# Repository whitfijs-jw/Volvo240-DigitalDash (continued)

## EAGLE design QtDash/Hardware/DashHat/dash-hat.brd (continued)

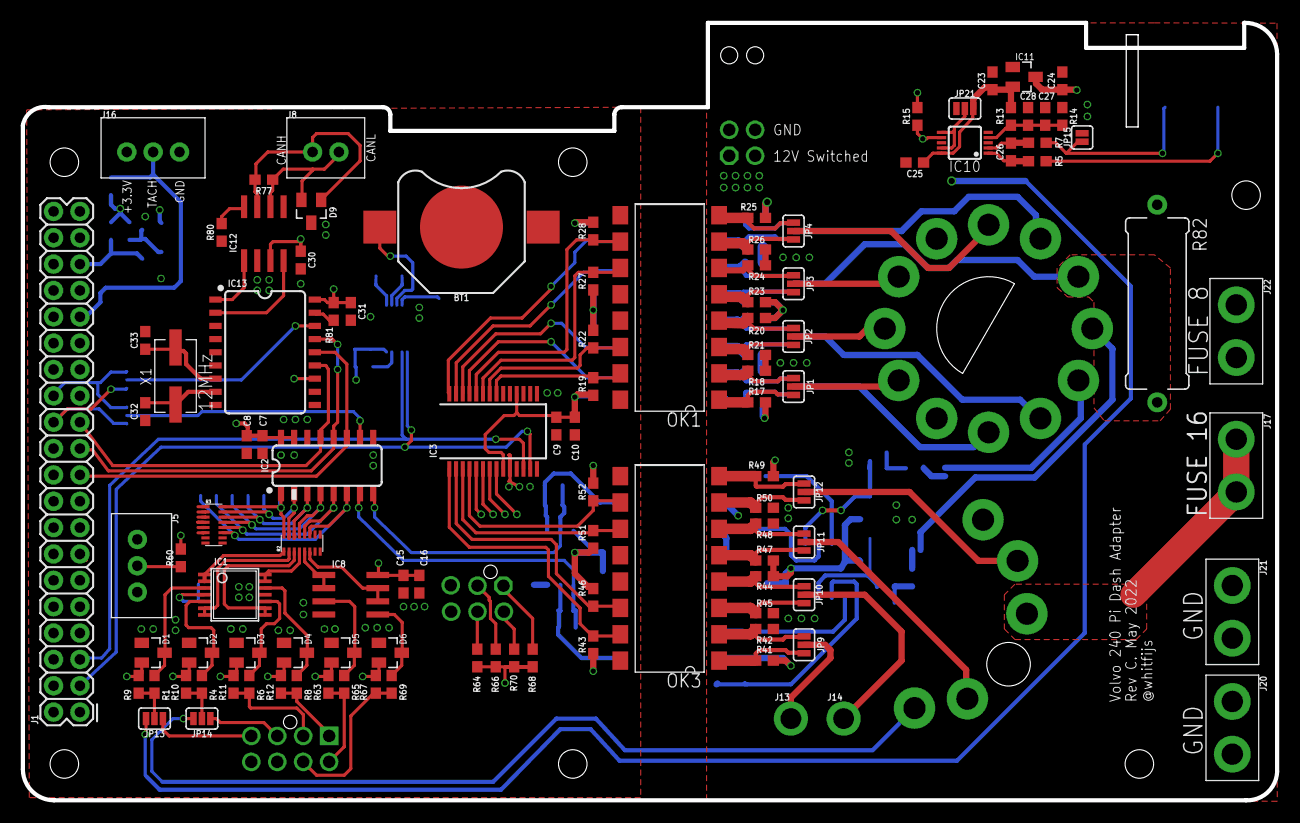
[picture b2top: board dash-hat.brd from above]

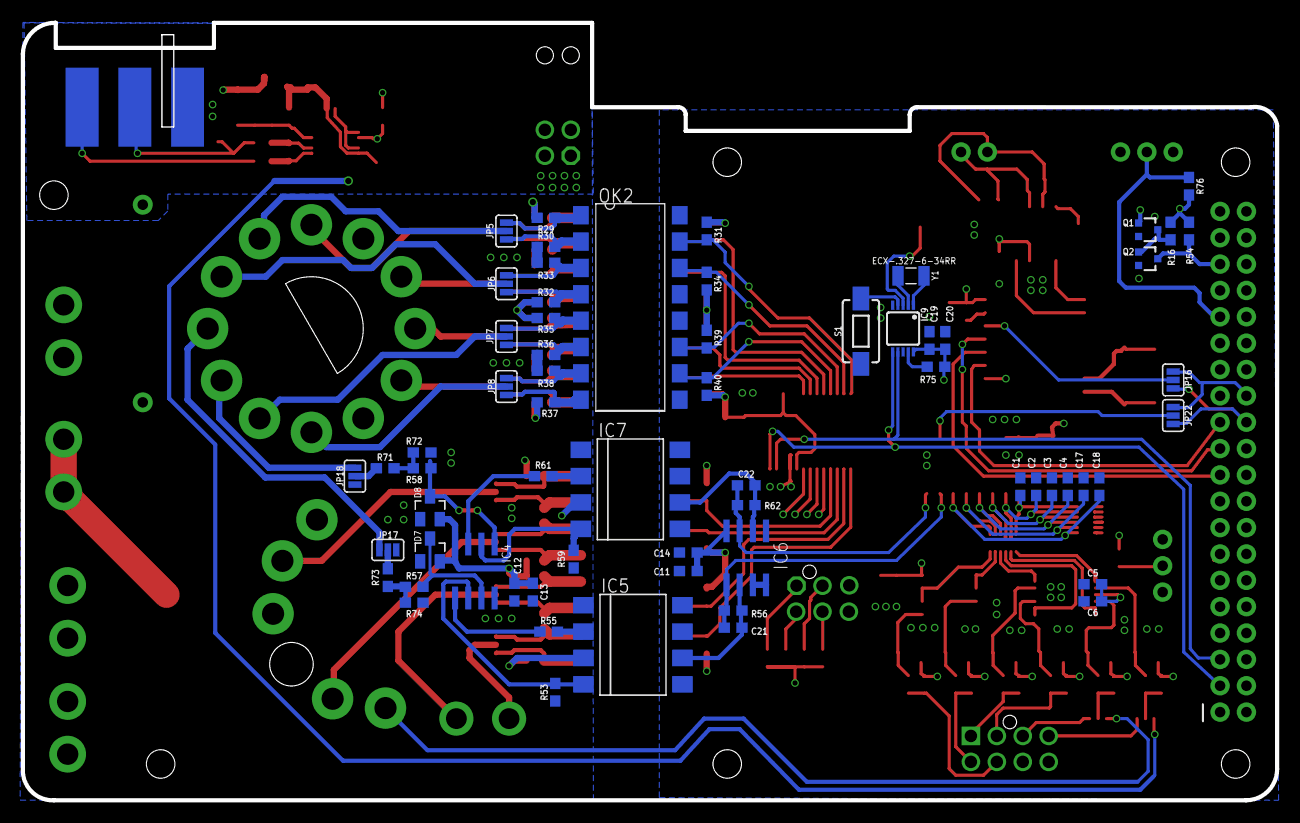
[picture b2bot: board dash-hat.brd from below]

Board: 4 copper layers, 120.9 x 74.9 mm, 179 parts (65 on the bottom side), 139 nets.

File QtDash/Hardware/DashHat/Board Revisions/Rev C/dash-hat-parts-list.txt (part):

Partlist exported from /home/whitfijs/git/Volvo240-DigitalDash/QtDash/Hardware/DashHat/dash-hat.sch at 5/19/22 10:42 PM

Qty Value                Device                              Package                      Parts                                                                                                        Description                                                                                                      MF        MPN           OC_FARNELL OC_NEWARK PROD_ID     SF_SKU    TOLERANCE VALUE          VOLTAGE
1                        BATTERY-12MM_SMD                    BATTCON_12MM                 BT1                                                                                                          Battery - Single Cell                                                                                                                                         BATT-08044  PRT-10592                                 
2                        CONN_01PTH_2MM                      1X01_2MM                     J13, J14                                                                                                     Single connection point. Often used as Generic Header-pin footprint for 0.1 inch spaced/style header connections                                                                                                    
1                        CONN_02                             1X02                         J8                                                                                                           Multi connection point. Often used as Generic Header-pin footprint for 0.1 inch spaced/style header connections                                                                                                     
4                        CONN_02PTH4                         1X02_XTRA_BIG                J17, J20, J21, J22                                                                                           Multi connection point. Often used as Generic Header-pin footprint for 0.1 inch spaced/style header connections                                                                                                     
8   100R                 RC0603JR-07100RL                    0603                         R1, R4, R6, R8, R57, R58, R65, R69                                                                                                                                                                                                                                                                         100R                  
6   100k 1%              RC0603FR-10100KL                    0603                         R53, R59, R71, R72, R73, R74                                                                                                                                                                                                                                                                               100k 1%               
20  100n                 CL10B104MB8NNNC                     0603                         C1, C2, C3, C4, C5, C7, C9, C11, C12, C15, C17, C18, C19, C21, C22, C23, C25, C27, C30, C31                                                                                                                                                                                                                100n           50V    
2   10k 1%               RC0603FR-1010KL                     0603                         R5, R7                                                                                                                                                                                                                                                                                                     10k 1%                
1   10u                  CL10B106MQ8NRNC                     0603                         C28                                                                                                                                                                                                                                                                                                        10u            6.3V   
1   120 1%               RC0603FR-07120RL                    0603                         R77                                                                                                                                                                                                                                                                                                        120 1%                
1   12MHz                ECS-120-20-3X-TR                    ECS                          X1                                                                                                                                                                                                                                                                                                         12MHz                 
1   15k                  YC248-JR-0715KL                     YC248                        R3                                                                                                                                                                                                                                                                                               5%        15k                   
15  1k                   RC0603JR-071KL                      0603                         R9, R10, R11, R12, R13, R14, R15, R63, R64, R66, R67, R68, R70, R75, R80                                                                                                                                                                                                                                   1k                    
1   1n                   CL10B102KB8NNWC                     0603                         C26                                                                                                                                                                                                                                                                                                        1n             50V    
8   1u                   CL10A105KA8NNNC                     0603                         C6, C8, C10, C13, C14, C16, C20, C24                                                                                                                                                                                                                                                                       1u             25V    
5   20k                  RC0603JR-0720KL                     0603                         R16, R54, R60, R76, R81                                                                                                                                                                                                                                                                                    20k                   
2   20k 1%               RC0603FR-0720KL                     0603                         R56, R62                                                                                                                                                                                                                                                                                                   20k 1%                
2   22p                  CL10C220JB81PNC                     0603                         C32, C33                                                                                                                                                                                                                                                                                                   22p            50V    
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
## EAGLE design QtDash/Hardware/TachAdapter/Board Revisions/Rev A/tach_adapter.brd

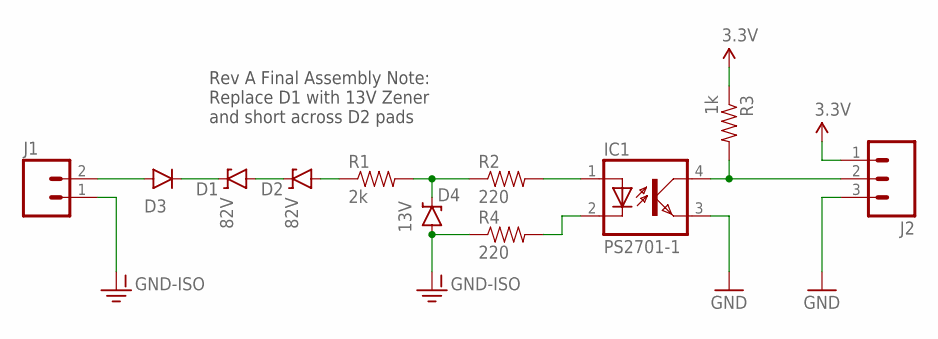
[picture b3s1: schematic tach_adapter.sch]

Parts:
D1, D2: 82V; SMB-DIODE
D3: DIODESMA; SMA-DIODE
D4: 13V; SMB-DIODE
IC1: PS2701-1; 4-SMD
J1: M02PTH3; 1X02_LONGPADS
J2: M03LONGPADS; 1X03_LONGPADS
R1: 2k; 1206
R2, R4: 220; 1206
R3: 1k; 1206

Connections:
3.3V: J2.1, R3.1
GND: IC1.3 (EMIT), J2.3
GND-ISO: D4.A, J1.1, R4.1
unnamed: D1.C, D3.C
unnamed: D1.A, D2.C
unnamed: D2.A, R1.1
unnamed: D4.C, R1.2, R2.1
unnamed: IC1.1 (A), R2.2
unnamed: IC1.2 (C), R4.2
unnamed: IC1.4 (COL), J2.2, R3.2
unnamed: D3.A, J1.2

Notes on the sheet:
Rev A Final Assembly Note: Replace D1 with 13V Zener and short across D2 pads

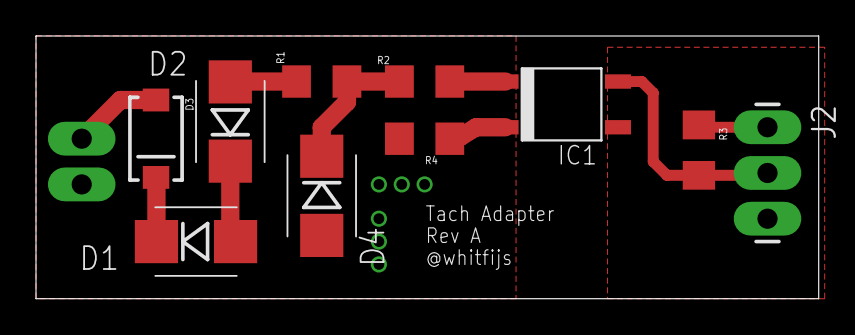
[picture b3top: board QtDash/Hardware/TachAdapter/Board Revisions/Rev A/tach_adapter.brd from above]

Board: 2 copper layers, 43.5 x 14.6 mm, 11 parts (0 on the bottom side), 11 nets.

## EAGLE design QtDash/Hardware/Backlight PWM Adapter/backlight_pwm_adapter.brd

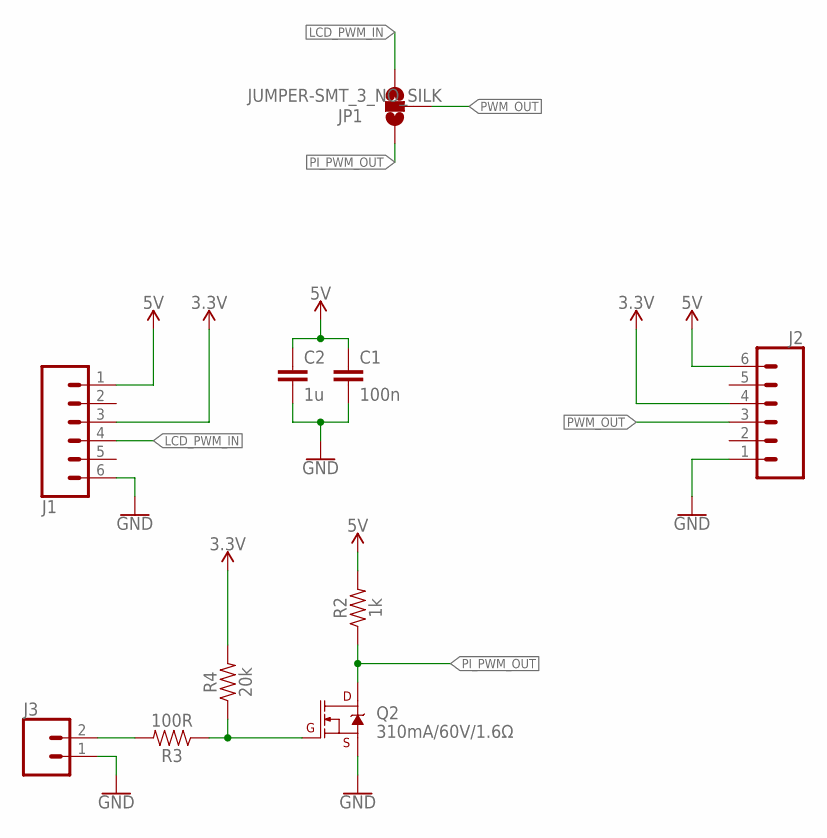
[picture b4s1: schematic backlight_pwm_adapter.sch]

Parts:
C1: 100n; 0603
C2: 1u; 0603
J1, J2: CONN_06; 140-506-417-060
J3: CONN_02; 1X02
JP1: JUMPER-SMT_3_NO_SILK; SMT-JUMPER_3_NO_SILK
Q2: 310mA/60V/1.6Ω; SOT323
R2: 1k; 0603
R3: 100R; 0603
R4: 20k; 0603

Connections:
3.3V: J1.3, J2.4, R4.2
5V: C1.1, C2.1, J1.1, J2.6, R2.2
GND: C1.2, C2.2, J1.6, J2.1, J3.1, Q2.2 (S)
LCD_PWM_IN: J1.4, JP1.3
unnamed: J3.2, R3.2
unnamed: Q2.1 (G), R3.1, R4.1
PI_PWM_OUT: JP1.1, Q2.3 (D), R2.1
PWM_OUT: J2.3, JP1.2

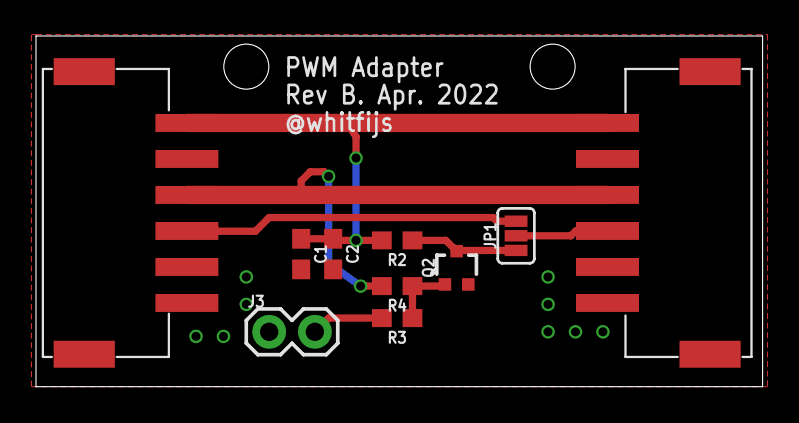
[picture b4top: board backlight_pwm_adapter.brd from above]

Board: 2 copper layers, 40.4 x 19.5 mm, 10 parts (0 on the bottom side), 8 nets.

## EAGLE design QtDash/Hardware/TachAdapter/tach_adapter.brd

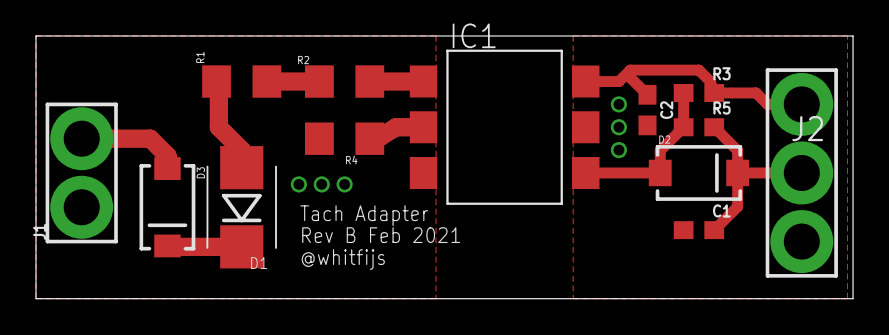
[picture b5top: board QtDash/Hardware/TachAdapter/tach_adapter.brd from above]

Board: 2 copper layers, 45.4 x 14.6 mm, 13 parts (0 on the bottom side), 11 nets.

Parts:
C1: 10n; 0603
C2: 100n; 0603
D1: 13V; SMB-DIODE
D2, D3: SMA-DIODE
IC1: H11L1SR2VM; 6-SMD
J1: 1X02_LARGE
J2: 1X03_LARGE
R1: 2k; 1206
R2, R4: 220; 1206
R3, R5: 1k; 0603

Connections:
3.3V: C2.1, IC1.6, J2.1, R3.1
GND: C1.2, C2.2, IC1.5, J2.3
GND-ISO: J1.1, R4.1
unnamed: D1.C, D3.C
unnamed: C1.1, D2.C, J2.2, R5.2
unnamed: D1.A, R1.1
unnamed: R1.2, R2.1
unnamed: IC1.1, R2.2
unnamed: IC1.2, R4.2
unnamed: D2.A, IC1.4, R3.2, R5.1
unnamed: D3.A, J1.2

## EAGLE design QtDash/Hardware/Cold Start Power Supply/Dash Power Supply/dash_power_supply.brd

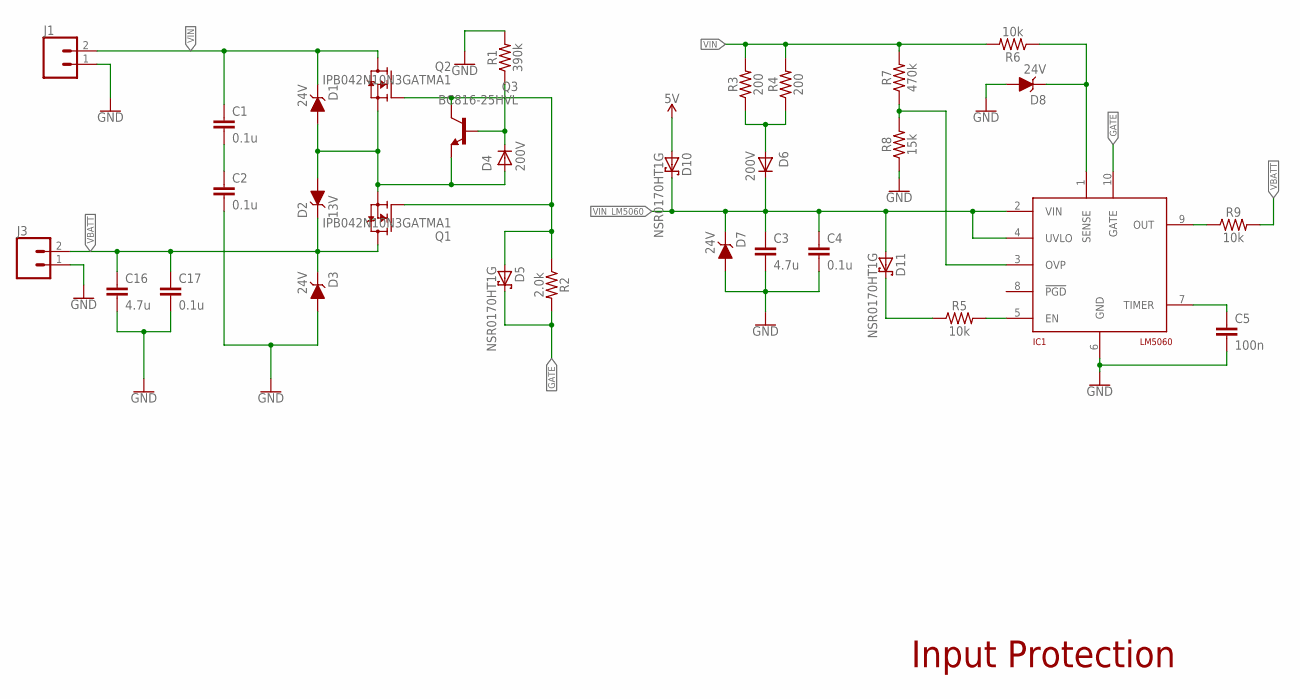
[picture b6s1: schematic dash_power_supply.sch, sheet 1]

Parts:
C1, C2, C4, C17: 0.1u; C1210
C3, C16: 4.7u; C1210
C5: 100n; 0603
D1, D3: 24V; SMC
D2: 13V; D0-219AB
D4, D6: 200V; D0-219AB
D5, D10, D11: NSR0170HT1G; SOD-323
D7, D8: 24V; SMA
IC1: LM5060; VSSOP-10
J1, J3: CONN_02PTH4; 1X02_XTRA_BIG
Q1, Q2: IPB042N10N3GATMA1; TO263
Q3: BC816-25HVL; SOT23
R1: 390k; 0603
R2: 2.0k; 0603
R3, R4: 200; 1206
R5, R6, R9: 10k; 0603
R7: 470k; 0603
R8: 15k; 0603

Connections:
5V: D10.A; also elsewhere on the board
G: D5.A, Q1.1 (G), Q2.1 (G), Q3.3 (C), R2.1
GATE: D5.C, IC1.10 (GATE), R2.2
GND: C2.2, C3.2, C4.2, C5.2, C16.2, C17.2, D3.A, D7.A, D8.A, IC1.6 (GND), J1.1, J3.1, R1.2, R8.1; also elsewhere on the board
unnamed: C1.2, C2.1
unnamed: IC1.5 (EN), R5.2
unnamed: D6.A, R3.1, R4.1
unnamed: D8.C, IC1.1 (SENSE), R6.1
unnamed: D4.C, Q3.1 (B), R1.1
unnamed: IC1.3 (OVP), R7.1, R8.2
unnamed: C5.1, IC1.7 (TIMER)
unnamed: IC1.9 (OUT), R9.1
unnamed: D11.C, R5.1
VBATT: C16.1, C17.1, D2.C, D3.C, J3.2, Q1.3 (D), R9.2; also elsewhere on the board
VIN: C1.1, D1.C, J1.2, Q2.3 (D), R3.2, R4.2, R6.2, R7.2
VIN_INTERNAL: D1.A, D2.A, D4.A, Q1.2 (S), Q2.2 (S), Q3.2 (E)
VIN_LM5060: C3.1, C4.1, D6.C, D7.C, D10.C, D11.A, IC1.2 (VIN), IC1.4 (UVLO)

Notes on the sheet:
Input Protection

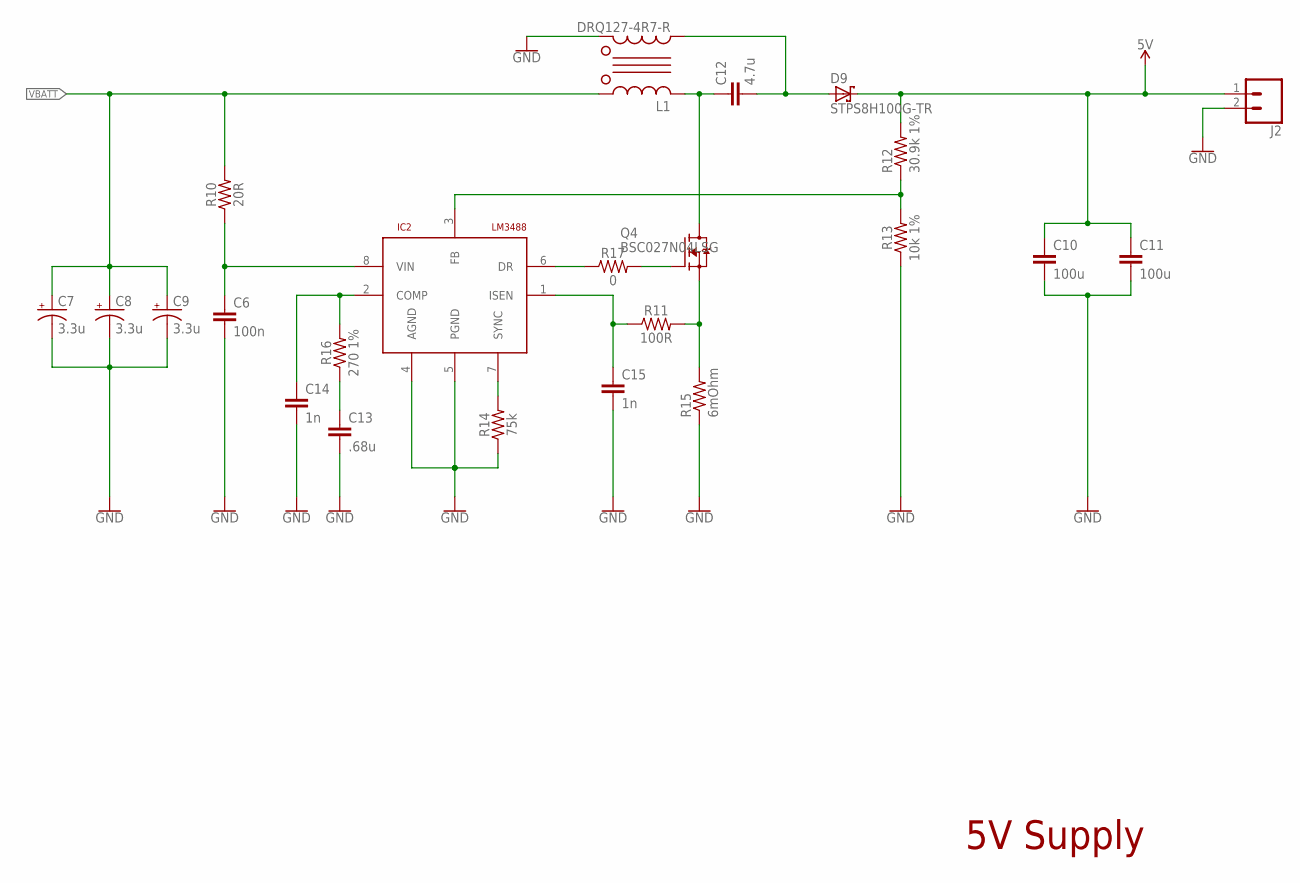
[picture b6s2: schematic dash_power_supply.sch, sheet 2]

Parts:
C6: 100n; 0603
C7, C8, C9: 3.3u; PANASONIC_C
C10, C11: 100u; C1210
C12: 4.7u; 0603
C13: .68u; 0603
C14, C15: 1n; 0603
D9: STPS8H100G-TR; TO263
IC2: LM3488; VSSOP-8
J2: CONN_02PTH4; 1X02_XTRA_BIG
L1: DRQ127-4R7-R; DRQ127
Q4: BSC027N04LSG; TDSON
R10: 20R; 0603
R11: 100R; 0603
R12: 30.9k 1%; R1206
R13: 10k 1%; 0603
R14: 75k; 0603
R15: 6mOhm; 3216
R16: 270 1%; 0603
R17: 0; 0603

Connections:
5V: C10.1, C11.1, D9.3 (C), J2.1, R12.2; also elsewhere on the board
GND: C6.2, C7.-, C8.-, C9.-, C10.2, C11.2, C13.2, C14.2, C15.2, IC2.4 (AGND), IC2.5 (PGND), J2.2, L1.2, R13.1, R14.1, R15.1; also elsewhere on the board
unnamed: Q4.4 (G), R17.2
unnamed: C6.1, IC2.8 (VIN), R10.1
unnamed: IC2.3 (FB), R12.1, R13.2
unnamed: IC2.6 (DR), R17.1
unnamed: C15.1, IC2.1 (ISEN), R11.1
unnamed: Q4.1 (S), Q4.2 (S), Q4.3 (S), R11.2, R15.2
unnamed: C12.1, L1.3, Q4.5 (D)
unnamed: C12.2, D9.2 (A), L1.4
unnamed: C14.1, IC2.2 (COMP), R16.2
unnamed: C13.1, R16.1
unnamed: IC2.7 (SYNC), R14.2
VBATT: C7.+, C8.+, C9.+, L1.1, R10.2; also elsewhere on the board

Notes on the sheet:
5V Supply

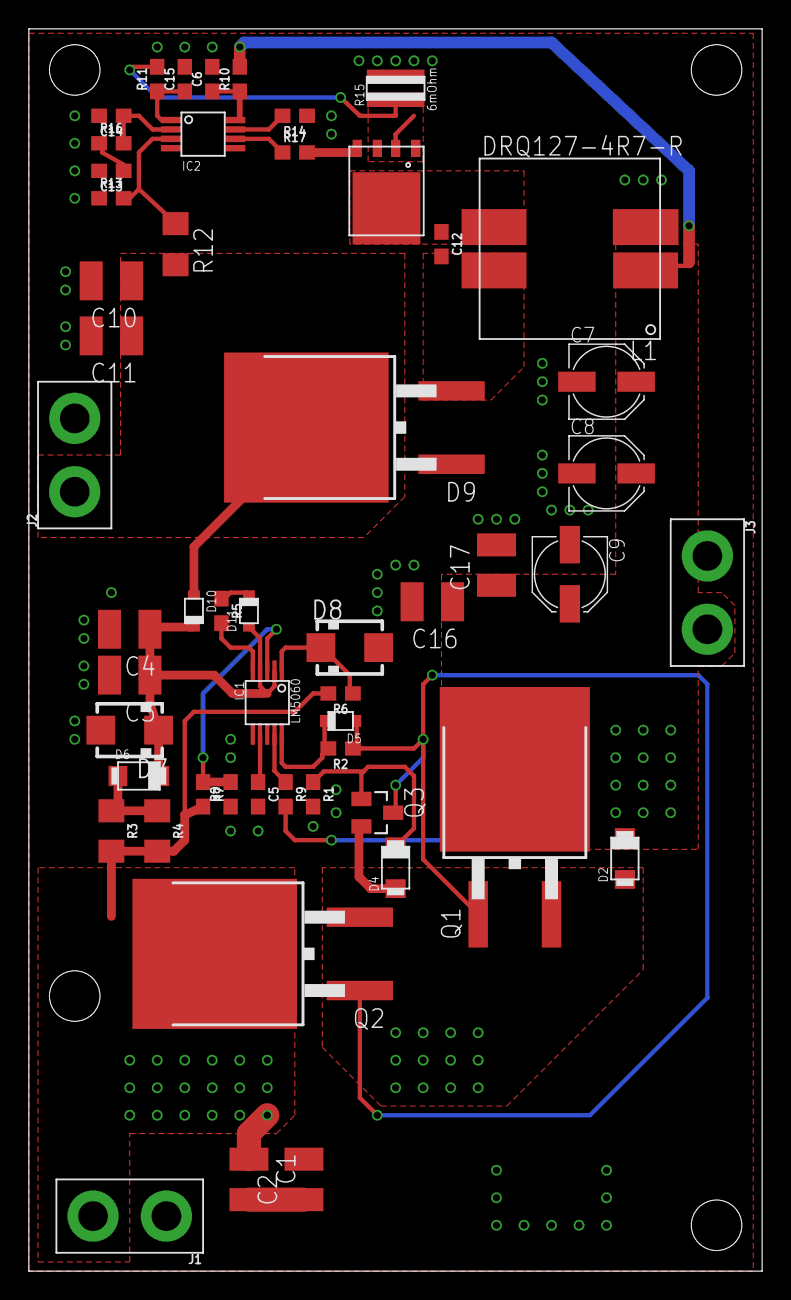
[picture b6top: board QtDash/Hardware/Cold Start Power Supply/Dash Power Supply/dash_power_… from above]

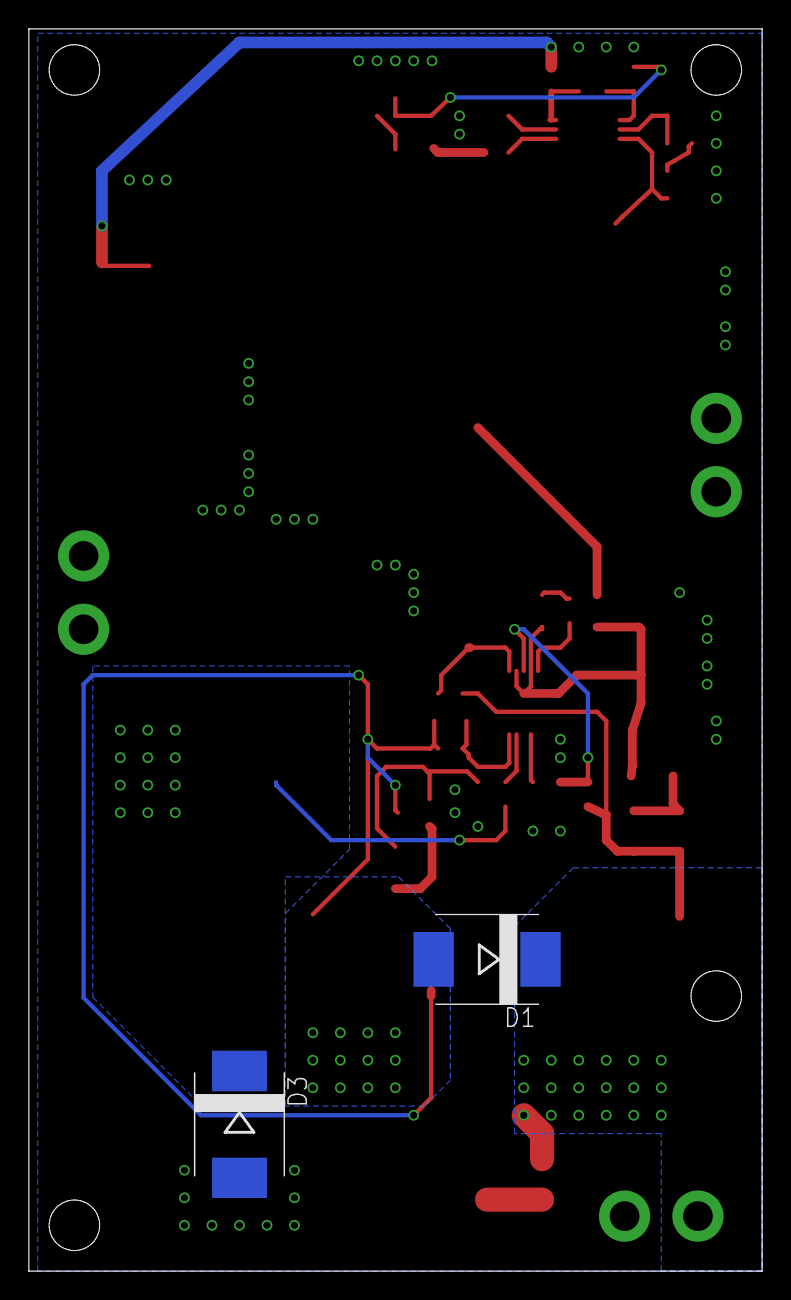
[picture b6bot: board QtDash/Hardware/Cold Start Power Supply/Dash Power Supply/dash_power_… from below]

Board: 2 copper layers, 50.8 x 86.0 mm, 55 parts (2 on the bottom side), 28 nets.

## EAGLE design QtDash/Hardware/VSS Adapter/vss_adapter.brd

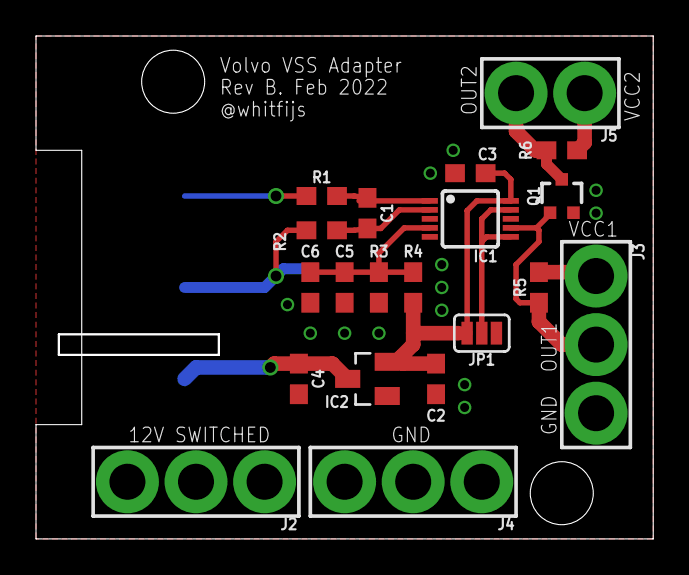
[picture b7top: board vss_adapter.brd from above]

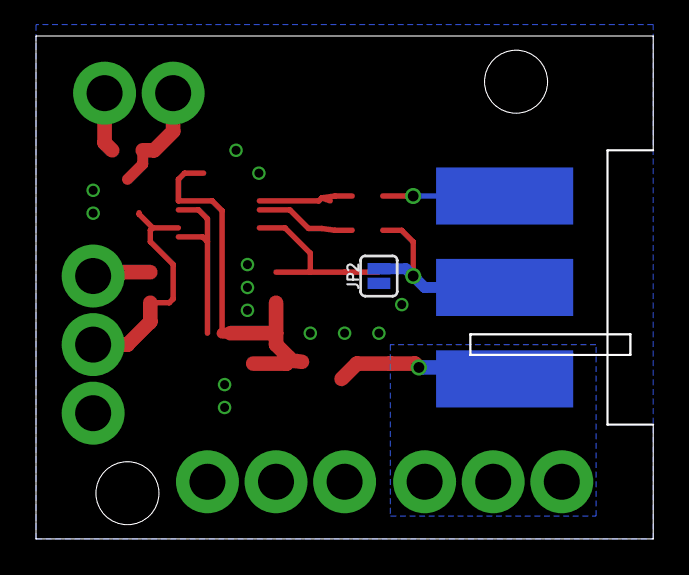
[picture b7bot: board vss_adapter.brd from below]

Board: 2 copper layers, 34.3 x 27.9 mm, 22 parts (2 on the bottom side), 13 nets.

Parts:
C1: 1n; 0603
C2, C3, C6: 100n; 0603
C4: 1u; 0603
C5: 10u; 0603
IC1: MAX9924; UMAX10
IC2: ZXTR2105FQ; SOT23
J1: VOLVO_CONN_VSS
J2, J3, J4: 1X03_LARGE
J5: 1X02_LARGE
JP1: ZERO_EN; SMT-JUMPER_3_NO_SILK
JP2: VSS-_GND; SMT-JUMPER_2_NO_SILK
Q1: 310mA/60V/1.6Ω; SOT323
R1, R2, R5, R6: 10k 1%; 0603
R3, R4: 1k; 0603

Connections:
5V: C2.1, C3.1, IC1.10, IC2.2, JP1.3, R4.1
GND: C2.2, C3.2, C4.2, C5.2, C6.2, IC1.5, IC2.1, J3.3, J4.1, J4.2, J4.3, JP1.1, JP2.1, Q1.2, R3.1
IN+: C1.1, IC1.1, R1.2
IN-: C1.2, IC1.2, R2.2
unnamed: C5.1, C6.1, IC1.4, R3.2, R4.2
unnamed: IC1.6, IC1.9, JP1.2
VCC_1: J3.1, R5.2
VCC_2: J5.1, R6.2
VIN: C4.1, IC2.3, J1.+, J2.1, J2.2, J2.3
VSS2_OUT: J5.2, Q1.3, R6.1
VSS+: J1.G, R1.1
VSS-: J1.1, JP2.2, R2.1
VSS_OUT: IC1.7, J3.2, Q1.1, R5.1

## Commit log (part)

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2022-01-21 - moved dash lights over to fast timer -- indicators might not respond to fast blinkers - droped medium timer to 150msec update
2022-01-23 topic/new-gauge-designs: - added clockwise/counterclockwise flag to gauge - 850 coolant gauge set to clockwise false so it works? Non lo so.
2022-01-25 bugfix/hardware-revA-issues: - added 0.5mm clearance to screen through holes
2022-01-26 bugfix/hardware-revA-issues: - first draft of mount
2022-01-27 bugfix/hardware-revA-issues: - added outputs solder points for fuse 16 and fuse 8 power - added 12V input solder points switched power? - added some ground vias on for 5V ground return path -- things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
2022-01-28 bugfix/hardware-revA-issues: - added squashfs rootfs to sd card image -- should be able to switch between ext4 and squash using cmdline.txt
2022-02-01 bugfix/hardware-revA-issues: - output of IL300s were oscillating under load -- added 100n capacitor (bodged on revA) - 12V inputs are only 0-3.3V signals -- K3 used to compensate for different for now
2022-02-03 bugfix/hardware-revA-issues: - fixed issues with clock seconds hand going the long way around when crossing from 59 to 0
2022-02-06 - copied revA version of pi adapter into /QtDash/Hardware/DashHat/Board Revisions/Rev A - generated gerbers and schematic pdf -- will need to modify the schematic to reflect what was actually built -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
2022-02-06 - update Board Revisions/Rev A schematic with final assembly values notes on final assembly
2022-02-10 topic/new-gauge-designs: - added shroud things on coolant and temp gauges in rsport cluster - updated fonts in rsport cluster svg
2022-02-11 topic/new-gauge-designs: - messing around with gauge borders - changed r-sport gauge needle color
2022-02-12 bugfix/hardware-revA-issues: - added supply only board for testing separately and more cheaply - added resistor values to cold start board library
2022-02-16 topic/switch-to-64-bit: - buildroot adjusted to work without rpi-userland packages - vc4 and v3d compiled into kernel - qml manually rotated 180 degrees - additional QT_QPA parameters added to init.d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
2022-02-17 bugfix/tach-adapter-updates: - added kicad project for tach adapter -- testing out kicad
2022-02-18 topic/new-gauge-designs: - updated bounds of 850r boost gauge
2022-02-19 topic/sensor-and-gauge-value-conditioning: - re-arranged dash initialization to avoid flippy text during boot
2022-02-20 topic/sensor-and-gauge-value-conditioning: - adjusted K3 value for 12V analog inputs, still not quite right -- consider using polynomial fits - adjusted decimal point values for gauges
2022-02-25 topic/component_optimization: - fixed issue with vss source signal/slot hookup - vss input now working -- tested with function generator
2022-03-01 topic/component-optimization: - 20k resistor on vin of power supply should have been 20R - fixed silk screen on cold start power supply - re-arranged components a via for cleaner return paths
2022-03-01 topic/component-optimization: - added some more output capacitors
2022-03-02 topic/more-accurate-gauge-needles: - tested on pi -- looks good - adjusted widths and colors in 740/940 layout
2022-03-03 topic/tach-adapter-udpates: - added kicad and eagle relevant gitignore fields
2022-03-05 - Filled in documentation for sensor configuration file (config.ini)
2022-03-06 bugfix/gauge-configs-dont-propagate: - ugly solution to convert internal sensor units to display units from config_gauges.ini
2022-03-08 - fixed spacing in README.md
2022-03-14 bugfix/analog-12v-input-linearity-issues: - added datasheets for IL300 alternatives - added .lib file for IL300
2022-03-26 topic/hardware-revb-support: - fixed text scaling for warning light
2022-03-30 topic/hardware-revb-support: - added writing of odometer value to pi dash - added Q_OBJECT to sensor_odometer to be able to use its writeOdometerValue signal
2022-04-06 topic/rpi4-support: - non-working configs
2022-04-12 topic/backlight-pwm-control: - added 50% backlight output on boot before app takes over (inittab) - changed cmdline.txt to boot from ext4 partition
2022-04-15 topic/rpi4-support: - moved preview image to top
2022-04-23 topic/backlight-pwm-control: - added (weak) pullup on PWM input to PWM adapter board - probably just need to make a backlight driver on the main board
2022-04-28 topic/hardware-revc: - replaced larger molex connector smaller molex connector
2022-04-29 topic/hardware-revc: - small layout changes to the main board
2022-05-04 topic/hardware-revc: - replaced dd with fbv in /sbin/preinit - tested pwm.h changes
2022-05-12 topic/hardware-revc: - added libsocketcan to target packages - added can-utils (to be removed later) - added Qt SerialBus package - added can0 interface bring up in etc/network
2022-05-13 topic/hardware-revc: - added beginngings of QCanBusDevice initialization
2022-05-20 topic/hardware-revc: - added parts list for rev c
2022-06-02 topic/hardware-revc: - gerbers generated for rev c - pcb's ordered from JLC pcb - rev c board preview images generated
2022-07-08 bugfix/hardware-revc-fixes: - added proper CAN support to rpi4 image -- working with MCP2515 on rev C hardware - fixed missing i2cdev package in rpi4 linux image -- mcp23017 working - MCP3208 moved t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
2022-10-03 bugfix/hardware-revc-fixes: - filled in more config unit tests -- temp sensor configs
2022-10-06 bugfix/hardware-revc-fixes: - changed 4-pin user input to 6-pin molex nano-fit connector to accomodate 3.3V and GND
2022-12-28 bugfix/hardware-revc-fixes: - added start out touch panel for 4 user inputs - fixed issues with host dash setup - changed changing of screen to key released and ignore duplicate events
2023-01-16 bugfix/hardware-revc-fixes: - user inputs pins are configurable - user input key mapping is somewhat configurable (Key_Left,Key_Right are needed to changed screens) - updated DashLights to accept gen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
2023-02-07 bugfix/hardware-revc-fixes: - initial value of resistive sensor previousValue was undefined
2023-02-16 feature/long-press-mapping-for-user-inputs-trip-odometer-resetting: - initial go at long press mapped to resetting trip counters - TODO: make long press mapping configurable
2023-03-14 feature-45: - key press on accessory screen cycles main screen (not configurable or very portable)
2023-03-15 feature-45: - added necessary changes to eglfs_hdmi.json and rcS enviroment variables setup to make touch display with with evdev
2023-03-16 feature-45: - added 740/940 style gauges to accessory screen layout -- side screen switches to 740/940 style gauges for 740 and 850 layouts - added 740 style oil temperature gauge
2023-03-16 feature-45: - added p1800 style boost/vaccum gauge and p1800 style clock assets -- no qml element yet
2023-03-18 feature-45: - added r-sport style accessory gauges
2023-04-06 feature/46-pi-zero-support: - added pi0w image configs -- uses rpi4 linux defconfig - image builds but needs to be tested
2023-11-28 50-map-sensor-atmospheric-offset-not-configurable: - updated readme for new options
2023-12-05 50-map-sensor-atmospheric-offset-not-configurable: - updated README to reflect changes in the config for the supply voltage
2023-12-05 topic/update-readme: - started updating readme with features - added more screenshots of dash styles
2023-12-07 topic/update-readme: - formatting changes
2023-12-08 topic/S60R-gauges: - added needle center image to Gauge.qml - added S60R style needle center, looks bad
2023-12-09 topic/S60R-gauges: - fixed voltmeter asset
2023-12-22 topic/documentation-update: - added tach adapter revision documentation for kicad and eagle
2023-12-22 topic/documentation-cleanup: - added 3d models for thickened main screen mounts - added accessory screen mount 3d models
2024-02-18 topic/early-240-cluster: - first draft of early 240 gauges
2024-02-20 topic/early-240-cluster: - started adding warning lights to early 240 layout
2024-02-21 topic/early-240-cluster: - added font for 240 style gauge - small update to gauge creator
2024-02-22 topic/early-240-cluster: - updated later 240-style with updated renders
2024-02-23 topic/early-240-cluster: - added accessory gauges to later 240 style svg
2024-02-24 topic/early-240-cluster: - attempted to get things sorted out on early 240 cluster
2024-02-26 topic/early-240-cluster: - updated README
2024-02-27 topic/early-240-cluster: - added border to early 240 cluster
2024-02-27 topic/early-240-cluster: - some changes to how the speedo model max and units get set
2024-03-03 topic/delegate-restructuring: - started add kph alternatives to speedometers
2024-03-03 topic/delegate-restructuring: - cleaned up resources that were not being used
2024-03-04 topic/delegate-restructuring: - fixed some gauge ranges in the rsport layout
2024-03-05 topic/delegate-restructuring: - fixed p1800 center gauge scaling
2024-03-10 55-adc-voltage-calculation-incorrect: - fixed issue with voltmeter calculation after testing in car
2024-03-11 topic/accessory-gauge-units: - updated 740/940 style oil temp gauge to include C units
2024-03-11 topic/accessory-gauge-units: - added support for "km/h" to be used as well as "kph"
2024-03-12 topic/accessory-gauge-units: - fixed integer truncating in gauge min/max values - added default values for given units to simplify config_gauges.ini
2024-03-13 topic/accessory-gauge-units: - updated README to include gauge configs
2024-03-14 topic/accessory-gauge-units: - fixed min/max angle on rsport coolant temp gauge - added clockwise option to gauge creator
2024-03-26 topic/accessory-gauge-units: - removed all traces of 140 rallye specific accessory gauges
2024-04-04 topic/config-cleanup: - cleaned up config class
2024-04-04 topic/config-cleanup: - event timer cleanup
2024-04-06 topic/config-cleanup: - ntc class cleanup
2024-04-07 topic/config-cleanup: - gps source cleanup
2024-04-10 topic/config-cleanup: - cleaned up sensor utils
2024-04-15 topic/gear-indicator: - starts on test for the gear indicator sensor
2024-06-18 topic/config-cleanup: - added more sanity checks to guage classes
2024-12-22 feature/63: - finally fixed absolute paths in dash host app
2024-12-27 bugfix/r-sport-cluster-boost-gauge-units: - made alternatives for r-sport cluster accessory boost gauge that don't have units
2025-02-01 task/cleanup-dash-class: - changed raw pointers to unique_ptr
2025-02-01 tasks/cleanup-dash-class: - made can sensors a vector of unique_ptr and touched... everything - getting can sensors now returns const pointer from unique_ptr, seems to be ok as it should have probabl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
2025-02-02 feature/72: - added screen rotation config option to config.ini - screen can be rotated to any arbirary angle (0 and 180 would be the obvious choices, but I won't screen shame) - frame buffer is not 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
2025-02-03 feature/70: - finalized build environment setup
2025-02-03 task/ll-cleanup: - LL adc driver cleanup
2025-02-04 task/ll-cleanup: - const cleanup
2025-02-04 task/gauge-sensor-cleanup: - lots of const ref and const function cleanup
2025-02-07 topic/config-sonarqube-cleanup: - fixed const and raw for loop
2025-02-09 topic/misc-cleanup: - make_unique updates
2025-03-08 topic/REV-D-hardware: - first draft of ADC driver for stm32u545 - todo: I2c peripheral implementation
2025-04-15 82-bom-missing: - added one more DNP to tach adapter board
2025-11-18 topic/S60R-gauges: - fixed S60R style boost gauge min/max
2025-11-20 topic/gear-indicator: - prototyping discrete bayes filter for estimating current gear - script for generating (poorly) simulated gear and rpm data
2025-11-25 topic/gear-indicator: - intermediate commit -- filling in gear predictor class
2025-12-05 topic/gear-indicator: - started filling in simple sanity check unit tests for GearPredictiveFilter
